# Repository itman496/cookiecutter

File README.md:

# cookiecutter
3lb Melybrain Battlebot

Teensy 4.0 based meltybrain using an accelerometer and IR beacons for tracking

Just keep in mind that all of this is a mess and how it works, I have no idea

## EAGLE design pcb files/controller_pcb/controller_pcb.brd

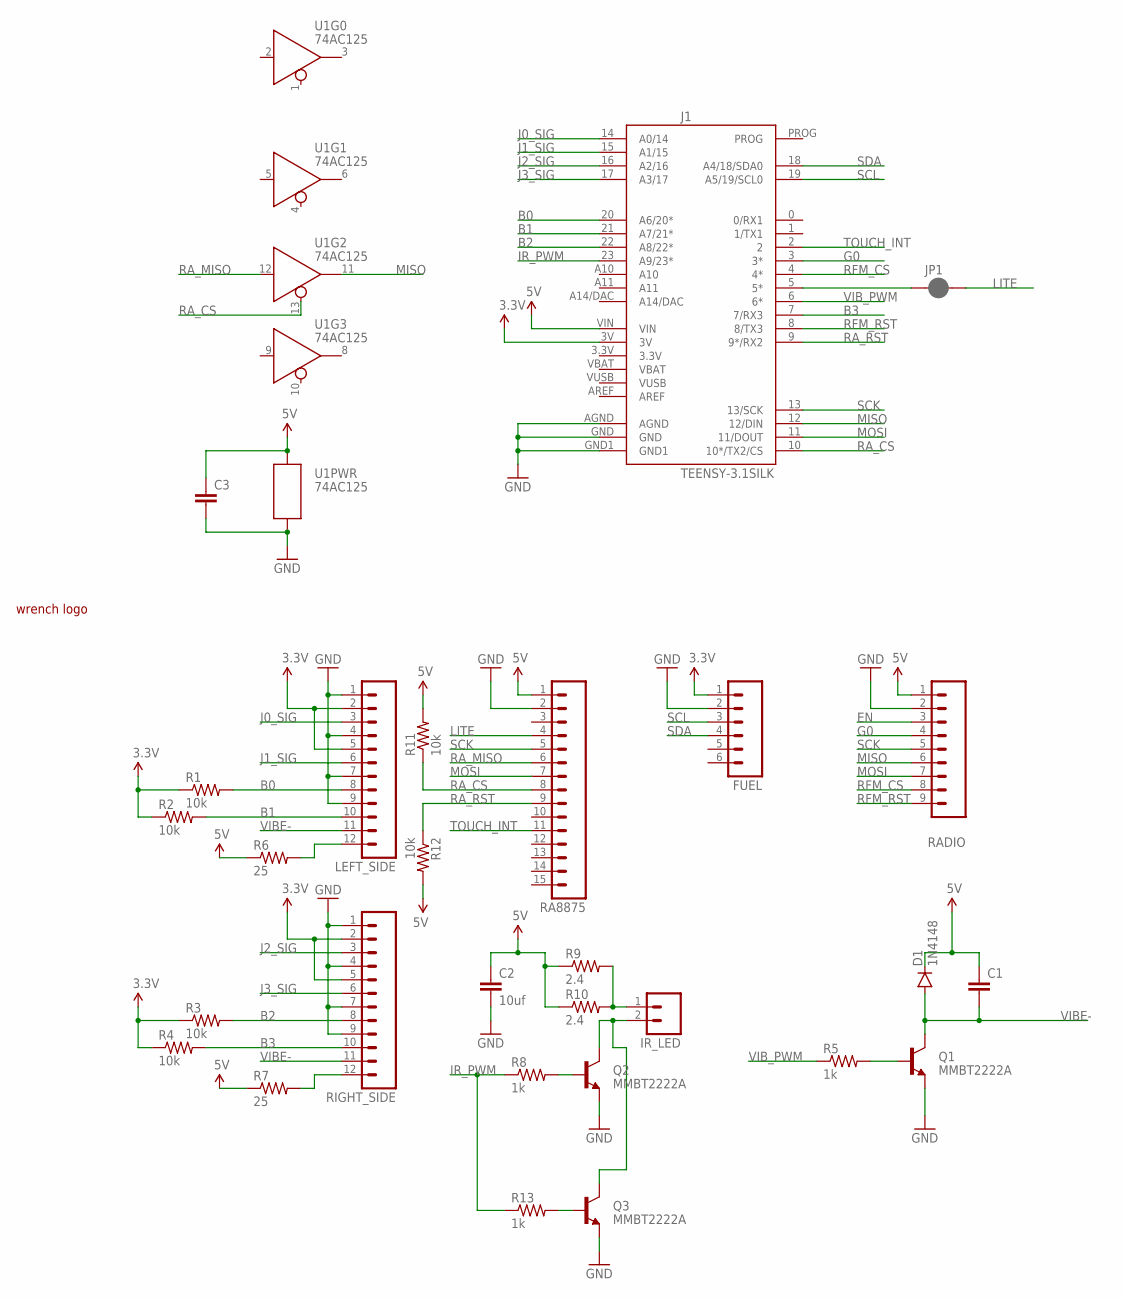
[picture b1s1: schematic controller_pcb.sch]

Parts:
C1, C3: CAP0805; 0805
C2: 10uf; 1206
D1: 1N4148; DIODE-1N4148
FUEL: M06LOCK_LONGPADS; 1X06_LOCK_LONGPADS
IR_LED: M02PTH3; 1X02_LONGPADS
J1: TEENSY-3.1SILK; TEENSY-3.1
JP1: JUMPER-PAD-2-NC_BY_PASTE; PAD-JUMPER-2-NC_BY_PASTE_YES_SILK
LEFT_SIDE: M12LONGPADS; 1X12_LONGPADS
Q1, Q2, Q3: MMBT2222A; SOT23-3
R1, R2, R3, R4, R11, R12: 10k; 0805
R5, R8, R13: 1k; 0805
R6, R7: 25; 0805
R9, R10: 2.4; AXIAL-0.5
RA8875: M15LOCK_LONGPADS; 1X15_LOCK_LONGPADS
RADIO: M09LOCK-LONGPADS; 1X09_LOCK_LONGPADS
RIGHT_SIDE: M12LONGPADS; 1X12_LONGPADS
U1: 74AC125; SO14
U$1: SMALL; WRENCHLOGO

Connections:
3.3V: FUEL.1, J1.3V, LEFT_SIDE.2, LEFT_SIDE.5, R1.1, R2.1, R3.1, R4.1, RIGHT_SIDE.2, RIGHT_SIDE.5
5V: C1.1, C2.1, C3.1, D1.C, J1.VIN, R6.1, R7.1, R9.P$1 (1), R10.P$1 (1), R11.2, R12.2, RA8875.1, RADIO.1, U1.14 (P$V+)
B0: J1.20 (A6/20*), LEFT_SIDE.8, R1.2
B1: J1.21 (A7/21*), LEFT_SIDE.10, R2.2
B2: J1.22 (A8/22*), R3.2, RIGHT_SIDE.8
B3: J1.7 (7/RX3), R4.2, RIGHT_SIDE.10
EN: RADIO.3
G0: J1.3 (3*), RADIO.4
GND: C2.2, C3.2, FUEL.2, J1.AGND, J1.GND, J1.GND1, LEFT_SIDE.1, LEFT_SIDE.4, LEFT_SIDE.7, LEFT_SIDE.9, Q1.2 (E), Q2.2 (E), Q3.2 (E), RA8875.2, RADIO.2, RIGHT_SIDE.1, RIGHT_SIDE.4, RIGHT_SIDE.7, RIGHT_SIDE.9, U1.7 (P$V-)
IR_PWM: J1.23 (A9/23*), R8.1, R13.1
J0_SIG: J1.14 (A0/14), LEFT_SIDE.3
J1_SIG: J1.15 (A1/15), LEFT_SIDE.6
J2_SIG: J1.16 (A2/16), RIGHT_SIDE.3
J3_SIG: J1.17 (A3/17), RIGHT_SIDE.6
LITE: JP1.2, RA8875.4
MISO: J1.12 (12/DIN), RADIO.6, U1.11 (Q)
MOSI: J1.11 (11/DOUT), RA8875.7, RADIO.7
unnamed: J1.5 (5*), JP1.1
unnamed: R7.2, RIGHT_SIDE.12
unnamed: LEFT_SIDE.12, R6.2
unnamed: Q1.1 (B), R5.2
unnamed: IR_LED.2, Q2.3 (C), Q3.3 (C)
unnamed: Q2.1 (B), R8.2
unnamed: IR_LED.1, R9.P$2 (2), R10.P$2 (2)
unnamed: Q3.1 (B), R13.2
RA_CS: J1.10 (10*/TX2/CS), R11.1, RA8875.8, U1.13 (!EN)
RA_MISO: RA8875.6, U1.12 (D)
RA_RST: J1.9 (9*/RX2), R12.1, RA8875.9
RFM_CS: J1.4 (4*), RADIO.8
RFM_RST: J1.8 (8/TX3), RADIO.9
SCK: J1.13 (13/SCK), RA8875.5, RADIO.5
SCL: FUEL.3, J1.19 (A5/19/SCL0)
SDA: FUEL.4, J1.18 (A4/18/SDA0)
TOUCH_INT: J1.2, RA8875.11
VIBE-: C1.2, D1.A, LEFT_SIDE.11, Q1.3 (C), RIGHT_SIDE.11
VIB_PWM: J1.6 (6*), R5.1

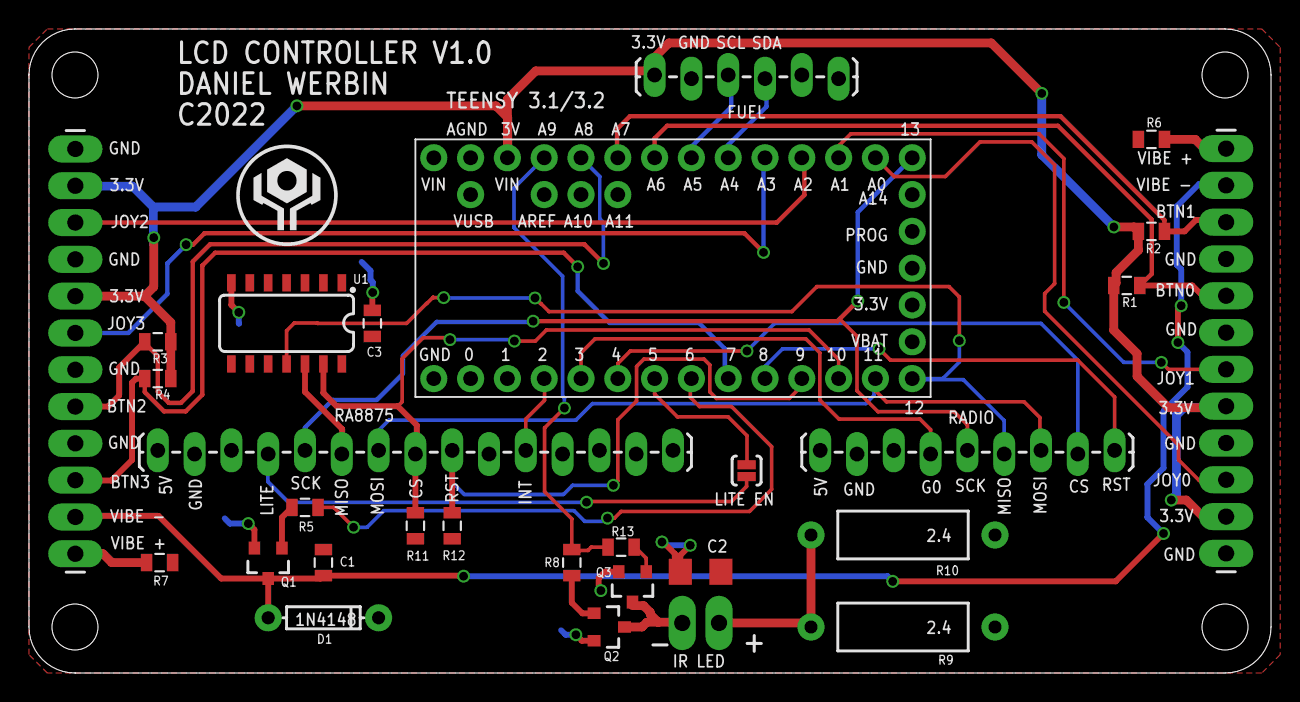
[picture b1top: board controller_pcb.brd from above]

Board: 2 copper layers, 85.7 x 44.5 mm, 30 parts (0 on the bottom side), 35 nets.

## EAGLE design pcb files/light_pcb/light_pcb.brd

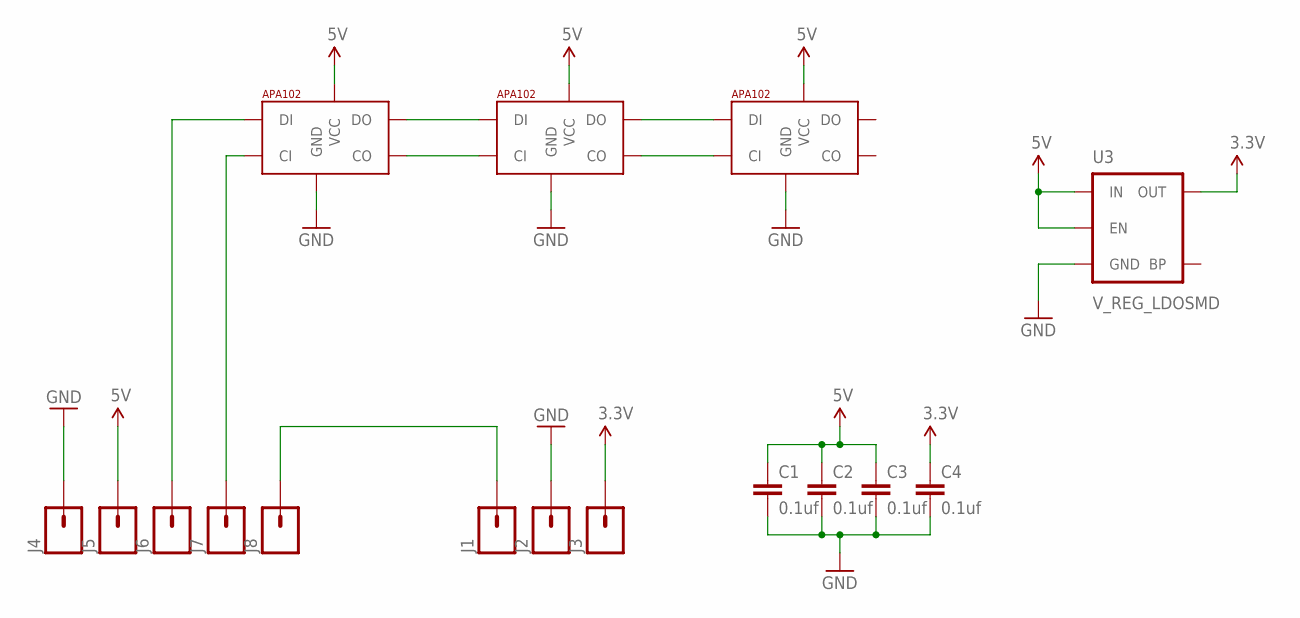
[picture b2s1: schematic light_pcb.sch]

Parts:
C1, C2, C3, C4: 0.1uf; 0805
J1, J2, J3, J4, J5, J6, J7, J8: M01SMD-4.5X1.5; PAD-1.5X4.5
U3: V_REG_LDOSMD; SOT23-5
U$1, U$2, U$3: APA1025050; APA102_5050

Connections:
3.3V: C4.1, J3.P$1, U3.5 (OUT)
5V: C1.1, C2.1, C3.1, J5.P$1, U3.1 (IN), U3.3 (EN), U$1.1 (VCC), U$2.1 (VCC), U$3.1 (VCC)
GND: C1.2, C2.2, C3.2, C4.2, J2.P$1, J4.P$1, U3.2 (GND), U$1.6 (GND), U$2.6 (GND), U$3.6 (GND)
unnamed: J6.P$1, U$1.4 (DI)
unnamed: J7.P$1, U$1.5 (CI)
unnamed: U$1.3 (DO), U$2.4 (DI)
unnamed: U$1.2 (CO), U$2.5 (CI)
unnamed: U$2.3 (DO), U$3.4 (DI)
unnamed: U$2.2 (CO), U$3.5 (CI)
unnamed: J1.P$1, J8.P$1

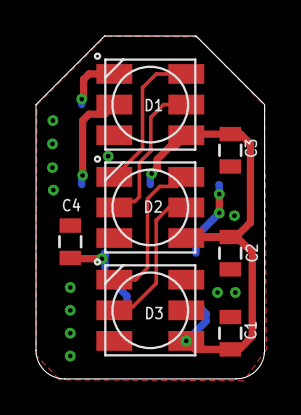
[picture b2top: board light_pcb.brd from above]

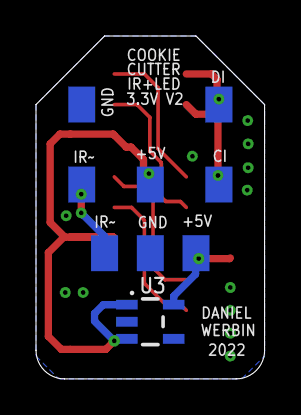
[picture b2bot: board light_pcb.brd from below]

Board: 2 copper layers, 12.7 x 19.1 mm, 16 parts (9 on the bottom side), 10 nets.

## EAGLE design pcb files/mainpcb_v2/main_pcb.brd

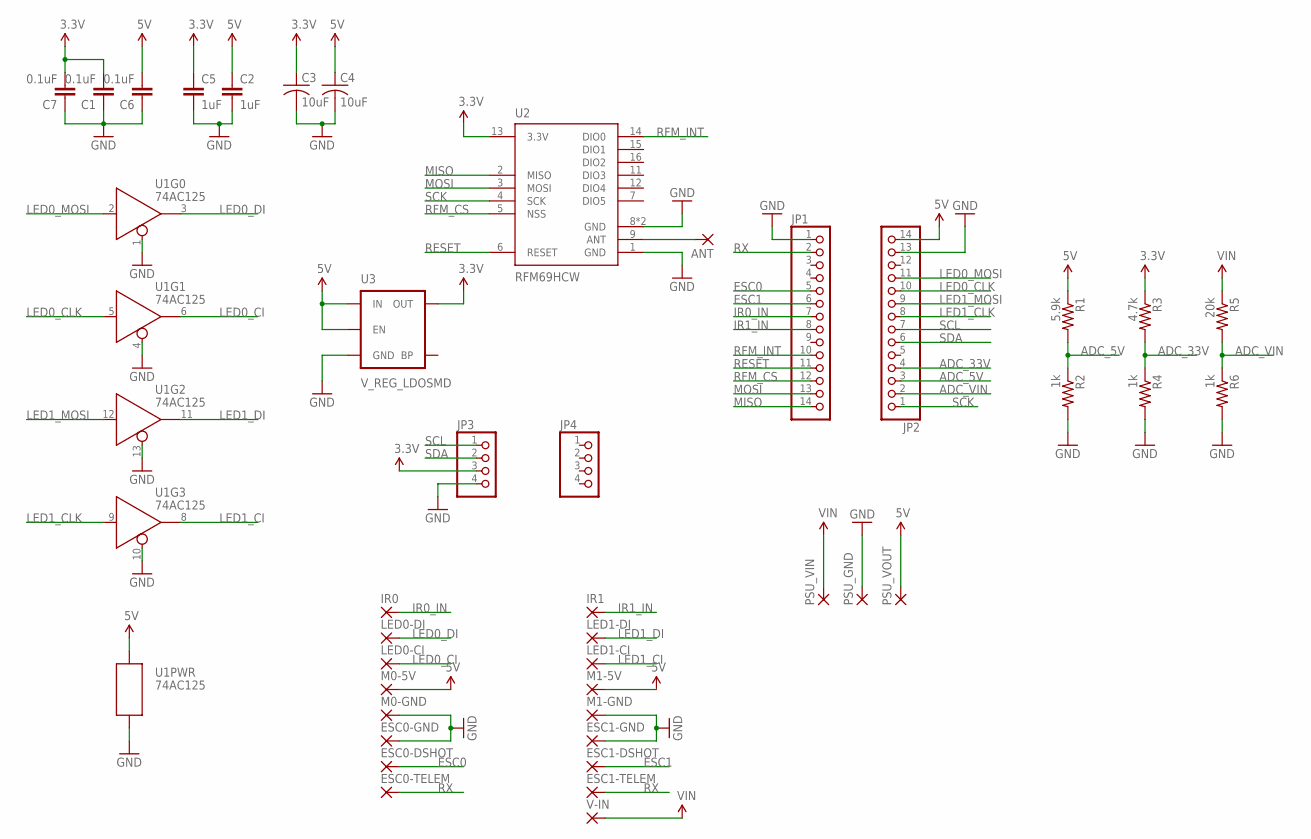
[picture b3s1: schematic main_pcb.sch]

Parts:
ANT: WIREPADSMD5-1,8; 5-1,8
C1, C6, C7: 0.1uF; 0805
C2, C5: 1uF; 0805
C3, C4: 10uF; C1206
ESC0-DSHOT, ESC0-GND, ESC0-TELEM, ESC1-DSHOT, ESC1-GND, ESC1-TELEM: WIREPADSMD5-1,8; 5-1,8
IR0, IR1: WIREPADSMD5-1,8; 5-1,8
JP1, JP2: PINHD-1X141X14_SMT; 1X14_SMT
JP3, JP4: PINHD-1X41X04_SMT; 1X04_SMT
LED0-CI, LED0-DI, LED1-CI, LED1-DI: WIREPADSMD5-1,8; 5-1,8
M0-5V, M0-GND, M1-5V, M1-GND: WIREPADSMD5-1,8; 5-1,8
PSU_GND: WIREPADSMD5-1,8; 5-1,8
PSU_VIN: WIREPADSMD5-1,8; 5-1,8
PSU_VOUT: WIREPADSMD5-1,8; 5-1,8
R1: 5.9k; 0805
R2, R4, R6: 1k; 0805
R3: 4.7k; 0805
R5: 20k; 0805
U1: 74AC125; SO14
U2: RFM69HCW; RFM69HCW-XXXS2
U3: V_REG_LDOSMD; SOT23-5
V-IN: WIREPADSMD5-1,8; 5-1,8

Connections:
3.3V: C1.2, C3.1, C5.1, C7.2, JP3.3, R3.1, U2.13 (3.3V), U3.5 (OUT)
5V: C2.1, C4.1, C6.2, JP2.14, M0-5V.1, M1-5V.1, PSU_VOUT.1, R1.1, U1.14 (P$V+), U3.1 (IN), U3.3 (EN)
ADC_5V: JP2.3, R1.2, R2.1
ADC_33V: JP2.4, R3.2, R4.1
ADC_VIN: JP2.2, R5.2, R6.1
ESC0: ESC0-DSHOT.1, JP1.5
ESC1: ESC1-DSHOT.1, JP1.6
GND: C1.1, C2.2, C3.2, C4.2, C5.2, C6.1, C7.1, ESC0-GND.1, ESC1-GND.1, JP1.1, JP2.13, JP3.4, M0-GND.1, M1-GND.1, PSU_GND.1, R2.2, R4.2, R6.2, U1.1 (!EN), U1.4 (!EN), U1.7 (P$V-), U1.10 (!EN), U1.13 (!EN), U2.1 (GND), U2.8 (GND), U2.10 (GND), U3.2 (GND)
IR0_IN: IR0.1, JP1.7
IR1_IN: IR1.1, JP1.8
LED0_CI: LED0-CI.1, U1.6 (Q)
LED0_CLK: JP2.10, U1.5 (D)
LED0_DI: LED0-DI.1, U1.3 (Q)
LED0_MOSI: JP2.11, U1.2 (D)
LED1_CI: LED1-CI.1, U1.8 (Q)
LED1_CLK: JP2.8, U1.9 (D)
LED1_DI: LED1-DI.1, U1.11 (Q)
LED1_MOSI: JP2.9, U1.12 (D)
MISO: JP1.14, U2.2 (MISO)
MOSI: JP1.13, U2.3 (MOSI)
unnamed: ANT.1, U2.9 (ANT)
RESET: JP1.11, U2.6 (RESET)
RFM_CS: JP1.12, U2.5 (NSS)
RFM_INT: JP1.10, U2.14 (DIO0)
RX: ESC0-TELEM.1, ESC1-TELEM.1, JP1.2
SCK: JP2.1, U2.4 (SCK)
SCL: JP2.7, JP3.1
SDA: JP2.6, JP3.2
VIN: PSU_VIN.1, R5.1, V-IN.1

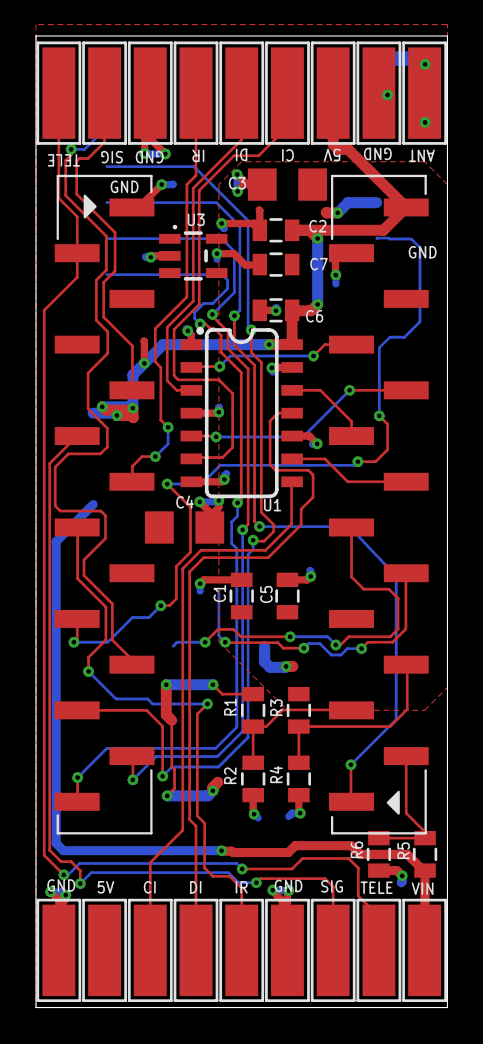
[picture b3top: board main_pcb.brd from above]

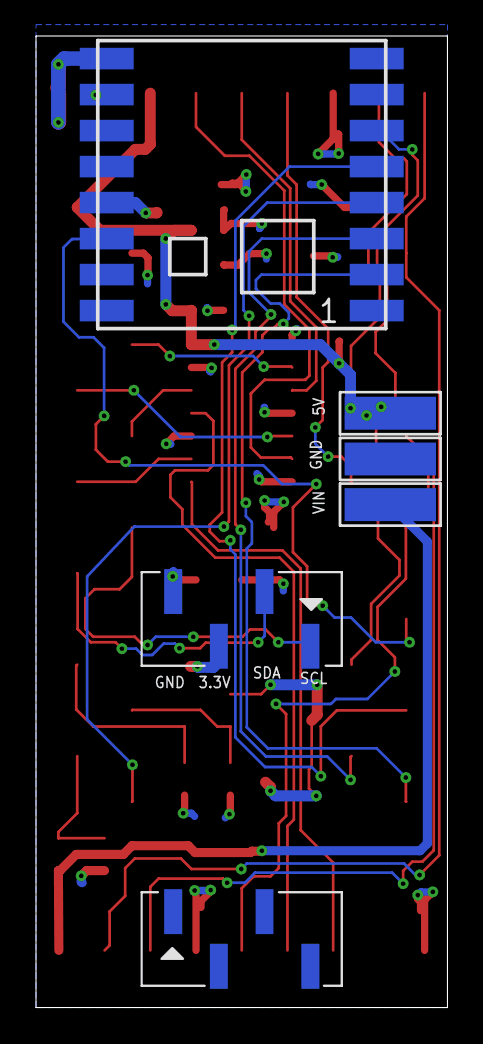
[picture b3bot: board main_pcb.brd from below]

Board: 2 copper layers, 22.9 x 54.0 mm, 41 parts (6 on the bottom side), 29 nets.

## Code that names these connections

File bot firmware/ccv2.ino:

//cookie cutter firmware v1.0

#include <TaskScheduler.h>
#include <H3LIS331DL.h>
#include <RFM69.h>
#include <Wire.h>
#include <SPI.h>
#include <movingAvg.h>
#include <MovingAverageFloat.h>
#include <FastLED.h>
#include <filters.h>

//filter stuff
const float cutoff_freq   = 5.0;  //Cutoff frequency in Hz
const float sampling_time = 0.001; //Sampling time in seconds.
IIR::ORDER  order  = IIR::ORDER::OD3; // Order (OD1 to OD4)

// Low-pass filter
Filter f(cutoff_freq, sampling_time, order);

//scheduler stuff
void accelreadcallback();
void voltagereadcallback();
void blinkercallback();
Task accelread(1, TASK_FOREVER, &accelreadcallback);
Task voltageread(100, TASK_FOREVER, &voltagereadcallback);
Task blinker(250, TASK_FOREVER, &blinkercallback);
Scheduler runner;   //scheduler object

//intervaltimer stuff
IntervalTimer controlTimer;

//led stuff
#define NUMLEDS       3
CRGB LEDS_0[NUMLEDS]; // Define the arrays of leds
CRGB LEDS_1[NUMLEDS];

//moving average stuff
movingAvg xAvg(50);
movingAvg yAvg(100);
movingAvg zAvg(100);
movingAvg rpmAvg(50);
movingAvg deltaAvg(10);

//H3LIS331 Accel stuff
//please get these value by running H3LIS331DL_AdjVal Sketch.
#define VAL_X_AXIS  360
#define VAL_Y_AXIS  98
#define VAL_Z_AXIS  371
#define ACCEL_RANGE 100
float CHIP_OFFSET = 14;
H3LIS331DL accel;


//GPIO
#define ESC0_OUT      3
#define ESC1_OUT      4
#define IR0_IN        5    
#define IR1_IN        6
#define LED0_MOSI     23
#define LED0_CLK      22
#define LED1_MOSI     21
#define LED1_CLK      20
#define ADC_VIN       A0  
#define ADC_5V        A1 
#define ADC_33V       A2 

//radio stuff
// Addresses for this node. CHANGE THESE FOR EACH NODE!
#define NETWORKID     0   // Must be the same for all nodes
#define MYNODEID      1   // My node ID
#define TONODEID      2   // Destination node ID
#define R_SS          10
#define R_INT         8
#define R_RST         9
// RFM69 frequency, uncomment the frequency of your module:
#define FREQUENCY     RF69_915MHZ
// AES encryption (or not):
#define ENCRYPT       false // Set to "true" to use encryption
#define ENCRYPTKEY    "TOPSECRETPASSWRD" // Use the same 16-byte key on all nodes
// Use ACKnowledge when sending messages (or not):
#define USEACK        false // Request ACKs or not
// Create a library object for our RFM69HCW module:
RFM69 radio(R_SS, R_INT, true);
//variables
const byte numChars = 65;
char receivedChars[numChars];
char tempChars[numChars];        // temporary array for use when parsing
// variables to hold the parsed data
char messageFromPC[numChars] = {0};
boolean newData = false;

//robot variables
volatile int errorState;
int headingCmd;  //heading you want to drive
int intensityCmd;  //how much did you push the stick
int joyScale = 256;  //scale of joysticks
int armed;
int throttleCmd;
int yawCmd;
int moveCmd;
int strafeCmd;
int leftTrimCmd;
int rightTrimCmd;
int blitzModeCmd;
int flipRobot;
int robotOrientation;  //0 is normal, 1 is flipped

int cmdValue;
int sentVarInt;
float sentVarFloat;
char sentVarString[30];

bool IR0_SENSE;
bool IR1_SENSE;

float VOLTS_5V;
float VOLTS_33V;
float VOLTS_BAT;
float xVel;
float yVel;
float zVel;

bool slowBlink;
bool fastBlink;

volatile int deltaInterval;
volatile int rpmInterval;
volatile int rpmPreviousMicros;
volatile int currentRPM;
volatile float calculatedRPM;
volatile float previousRPM;
volatile float deltaRPM;
int rpmTrim;  //trim to stop drift
bool trimLock;
float filteredRPM;  //rpm low pass filter stuff


int driveOffset = 120;  //how many degrees to wait to start giving power
int driveDuration = 180;  //how many degrees is a power phase
volatile int degreeSlice;  //amount of microseconds per degree at current speed
volatile bool irLedFlag;  //controls ir led color
volatile bool aimLedFlag;  //controls aim led color
volatile int accelInterval;  //control loop uses this to only calculate rpm every 10 loops
volatile int indexMicros;  //start of cycle time
volatile int rotationPeriod;  //calculated rotation length
volatile int futureIndex;  //predicted next centerpoint
volatile int robotMode;
volatile int aimWaypoint;  //waypoint for aim leds
volatile int aimLedStartTime;  //start of time to light up aiming LED
volatile int aimLedEndTime;    //time to turn aim LED back off
volatile int driveWaypoint;  //waypoint for drive
volatile int throttleUpTime0;   //time to throttle motor 0 up
volatile int throttleDownTime0; //time to throttle motor 0 down
volatile int throttleUpTime1;   //time to throttle motor 1 up
volatile int throttleDownTime1; //time to throttle motor 1 down

void setup() {
  Serial.begin(115200);
  Wire.begin();
  
  accel.init();
  accel.importPara(VAL_X_AXIS,VAL_Y_AXIS,VAL_Z_AXIS);
  accel.setODR(H3LIS331DL_ODR_1000Hz);
  accel.setFullScale(H3LIS331DL_FULLSCALE_2);
   
  
  //radio init
  pinMode(R_RST, OUTPUT);
  digitalWrite(R_RST, LOW); digitalWrite(R_RST, HIGH); delay(10); digitalWrite(R_RST, LOW); delay(10); // manual reset
  radio.initialize(FREQUENCY, MYNODEID, NETWORKID);
  radio.setHighPower(); // Always use this for RFM69HCW
  //pinMode(R_INT,INPUT_PULLUP);
  
  //moving average init
  xAvg.begin();
  yAvg.begin();
  zAvg.begin();
  rpmAvg.begin();
  deltaAvg.begin();

  //gpio init
  pinMode(ESC0_OUT, OUTPUT);
  pinMode(ESC1_OUT, OUTPUT);
  pinMode(IR0_IN, INPUT);
  pinMode(IR1_IN, INPUT);
  pinMode(LED0_MOSI, OUTPUT);
  pinMode(LED0_CLK, OUTPUT);
  pinMode(LED1_MOSI, OUTPUT);
  pinMode(LED1_CLK, OUTPUT);

  attachInterrupt(digitalPinToInterrupt(IR0_IN),ir_isr,CHANGE);  //attach interrupt for IR

  controlTimer.priority(200);  //set to lower priority on stuff
  controlTimer.begin(control_loop, 100); //starts interrupt routine 10khz
  
  //leds init
  FastLED.addLeds<DOTSTAR, LED0_MOSI, LED0_CLK, RBG>(LEDS_0, NUMLEDS);  // BGR ordering is typical
  FastLED.addLeds<DOTSTAR, LED1_MOSI, LED1_CLK, RBG>(LEDS_1, NUMLEDS);  // BGR ordering is typical

  //scheduler init
  runner.addTask(accelread);
  runner.addTask(voltageread);
  runner.addTask(blinker);
  accelread.enable();
  voltageread.enable();
  blinker.enable();
}

void loop() {
  runner.execute();  //runs scheduler system

  calc_rpm();
  radio_routine();

  if(calculatedRPM < 150) {
    led_set0(255,255,255);  led_set1(255,255,255);  
  } 
  if(throttleCmd > 300 && calculatedRPM < 150) {
    led_set0(0,0,0);  led_set1(0,0,0);  
  }
  //if(IR0_SENSE == true) {
  //  led_set0(0,255,0);
  //}
  //if(IR1_SENSE == true) {
  //  led_set1(0,255,0);
  //}
  /*
  if(aimLedFlag == true && calculatedRPM > 0) {
    led_set0(0,0,255);
  }
  if(aimLedFlag == false && calculatedRPM > 0) {
    led_set0(0,0,0);
  }
  */
  FastLED.show();
  debug_values();
  //delay(1000);
}

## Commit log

2023-02-12 initial upload
2023-02-12 name change so arduino IDE works
2023-02-12 more changes, I'm stupid
2023-02-12 uploading more files, learning github :)
2023-02-12 more organization
2023-02-12 uploading dshot testing
2023-02-16 generates packets on the fly instead of ahead of time, telemetry works properly in theory
2023-02-17 fully tested and working with both escs now

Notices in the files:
parts and their libraries:
SparkFun-Capacitors: Licensing: Creative Commons ShareAlike 4.0 International - https://creativecommons.org/licenses/by-sa/4.0
